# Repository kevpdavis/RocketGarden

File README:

This is a repository for my rocket related projects.

You'll find designs and design tools for rockets, parachutes, printed circuit boards, motors, and whatever else I dabble in.

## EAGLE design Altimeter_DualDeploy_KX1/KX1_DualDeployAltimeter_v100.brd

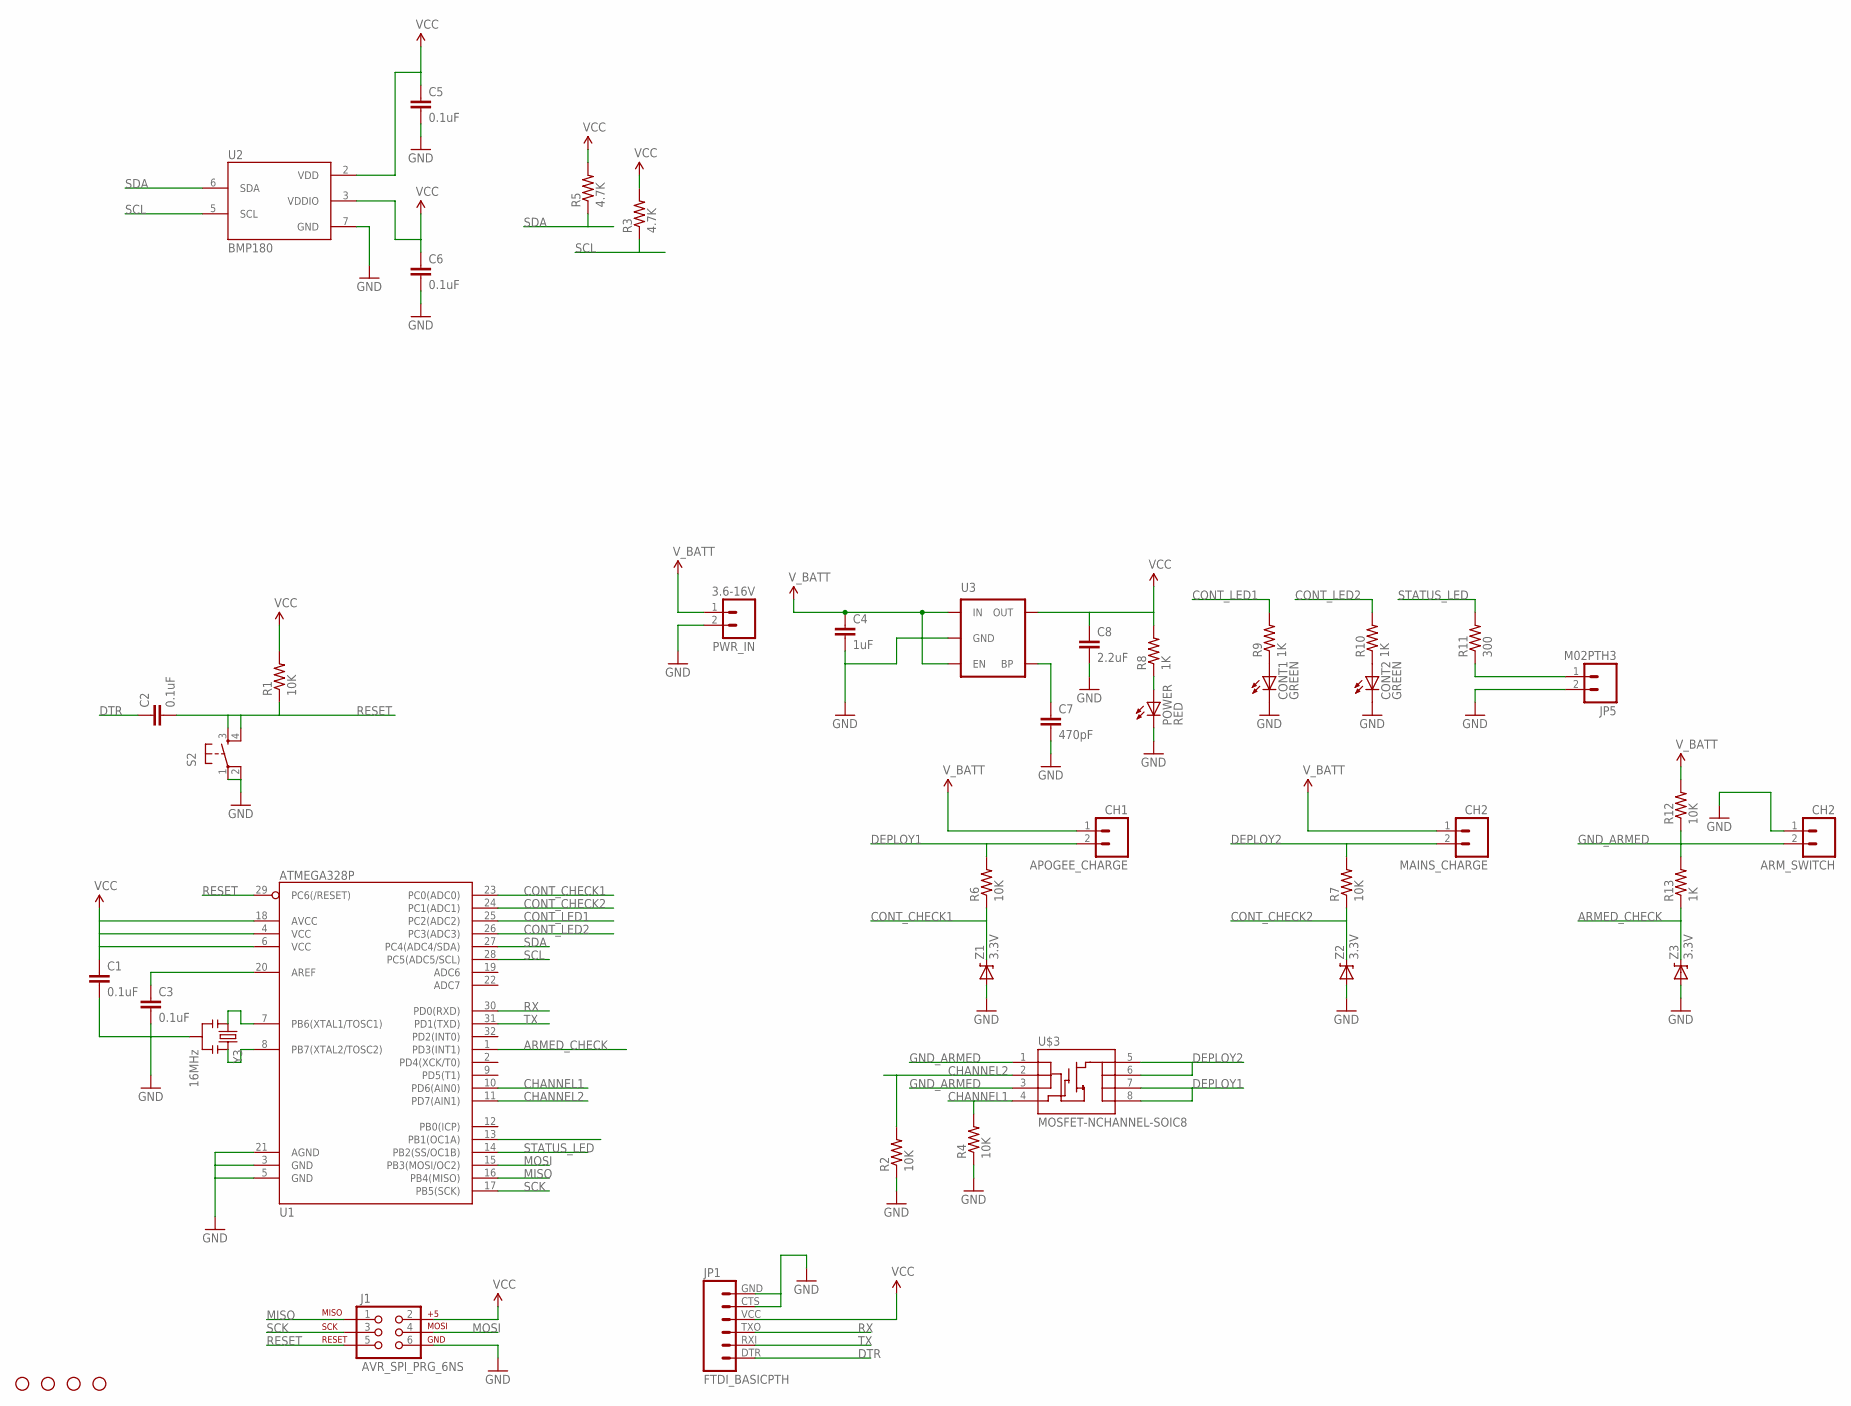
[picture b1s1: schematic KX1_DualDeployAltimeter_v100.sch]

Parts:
APOGEE_CHARGE: CH1; 1X02_LONGPADS
ARM_SWITCH: CH2; 1X02_LONGPADS
C1, C2, C3, C5, C6: 0.1uF; 0603-CAP
C4: 1uF; 0603-CAP
C7: 470pF; 0603-CAP
C8: 2.2uF; 0603-CAP
CONT1, CONT2: GREEN; LED-0603
J1: AVR_SPI_PRG_6NS; 2X3-NS
JP1: FTDI_BASICPTH; FTDI_BASIC
JP5: M02PTH3; 1X02_LONGPADS
MAINS_CHARGE: CH2; 1X02_LONGPADS
POWER: RED; LED-0603
PWR_IN: 3.6-16V; 1X02_LONGPADS
R1, R2, R4, R6, R7, R12: 10K; 0603-RES
R3, R5: 4.7K; 0603-RES
R8, R9, R10, R13: 1K; 0603-RES
R11: 300; 0603-RES
S2: TAC_SWITCHPTH; TACTILE-PTH
STANDOFF1, STANDOFF2, STANDOFF3, STANDOFF4: STAND-OFF
U1: ATMEGA328P; TQFP32-08
U2: BMP180
U3: MIC52053.3V; SOT23-5
U$3: MOSFET-NCHANNEL-SOIC8; SO08
Y3: 16MHz; RESONATOR-SMD
Z1, Z2, Z3: 3.3V; SOD-323

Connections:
ARMED_CHECK: R13.1, U1.1 (PD3(INT1)), Z3.1 (C)
CHANNEL1: R4.2, U1.10 (PD6(AIN0)), U$3.4 (G)
CHANNEL2: R2.2, U1.11 (PD7(AIN1)), U$3.2 (S)
CONT_CHECK1: R6.1, U1.23 (PC0(ADC0)), Z1.1 (C)
CONT_CHECK2: R7.1, U1.24 (PC1(ADC1)), Z2.1 (C)
CONT_LED1: R9.2, U1.25 (PC2(ADC2))
CONT_LED2: R10.2, U1.26 (PC3(ADC3))
DEPLOY1: APOGEE_CHARGE.2, R6.2, U$3.7 (D), U$3.8 (D)
DEPLOY2: MAINS_CHARGE.2, R7.2, U$3.5 (D), U$3.6 (D)
DTR: C2.1, JP1.DTR (1)
GND: ARM_SWITCH.1, C1.2, C3.2, C4.2, C5.2, C6.2, C7.2, C8.2, CONT1.C, CONT2.C, J1.6, JP1.CTS (5), JP1.GND (6), JP5.2, POWER.C, PWR_IN.2, R2.1, R4.1, S2.1, S2.2, U1.3 (GND), U1.5 (GND), U1.21 (AGND), U2.7 (GND), U3.2 (GND), Y3.2, Z1.2 (A), Z2.2 (A), Z3.2 (A)
GND_ARMED: ARM_SWITCH.2, R12.1, R13.2, U$3.1 (S), U$3.3 (S)
MISO: J1.1, U1.16 (PB4(MISO))
MOSI: J1.4, U1.15 (PB3(MOSI/OC2))
unnamed: POWER.A, R8.1
unnamed: CONT1.A, R9.1
unnamed: CONT2.A, R10.1
unnamed: C3.1, U1.20 (AREF)
unnamed: U1.7 (PB6(XTAL1/TOSC1)), Y3.1
unnamed: U1.8 (PB7(XTAL2/TOSC2)), Y3.3
unnamed: JP5.1, R11.1
unnamed: C7.1, U3.4 (BP)
RESET: C2.2, J1.5, R1.1, S2.3, S2.4, U1.29 (PC6(/RESET))
RX: JP1.TXO (3), U1.30 (PD0(RXD))
SCK: J1.3, U1.17 (PB5(SCK))
SCL: R3.1, U1.28 (PC5(ADC5/SCL)), U2.5 (SCL)
SDA: R5.1, U1.27 (PC4(ADC4/SDA)), U2.6 (SDA)
STATUS_LED: R11.2, U1.14 (PB2(SS/OC1B))
TX: JP1.RXI (2), U1.31 (PD1(TXD))
VCC: C1.1, C5.1, C6.1, C8.1, J1.2, JP1.VCC (4), R1.2, R3.2, R5.2, R8.2, U1.4 (VCC), U1.6 (VCC), U1.18 (AVCC), U2.2 (VDD), U2.3 (VDDIO), U3.5 (OUT)
V_BATT: APOGEE_CHARGE.1, C4.1, MAINS_CHARGE.1, PWR_IN.1, R12.2, U3.1 (IN), U3.3 (EN)

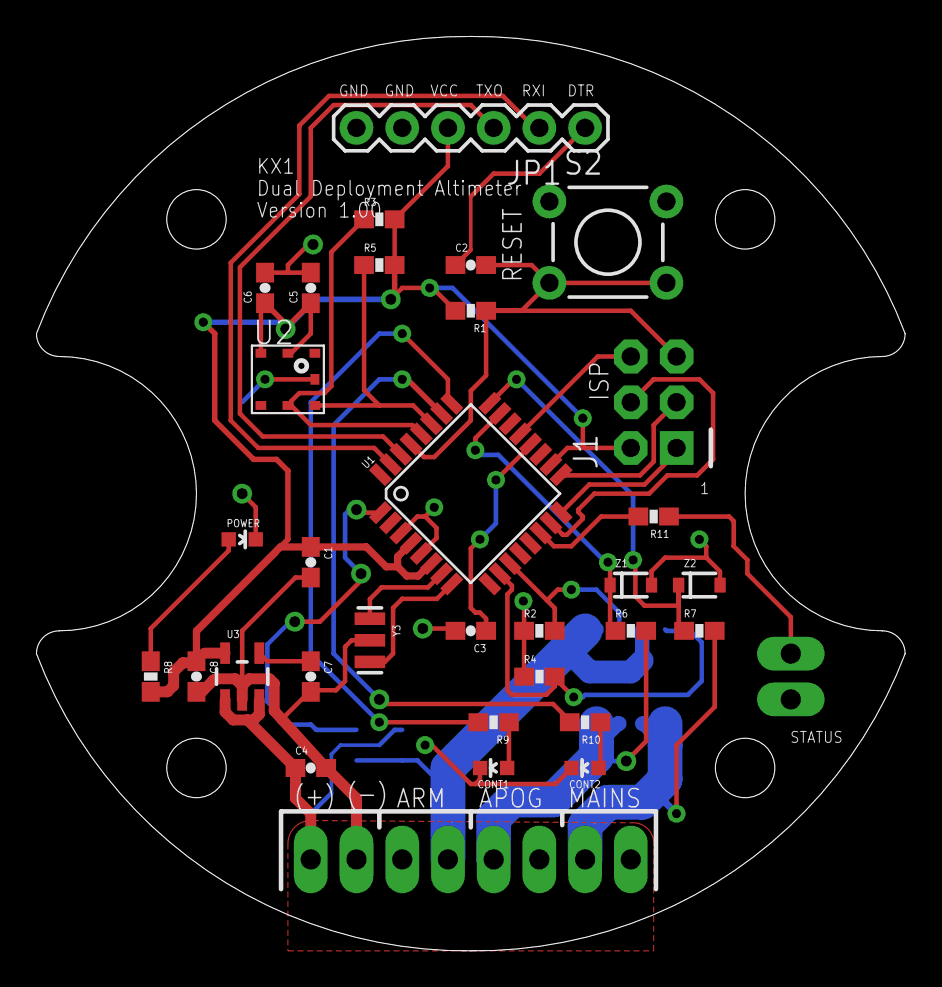
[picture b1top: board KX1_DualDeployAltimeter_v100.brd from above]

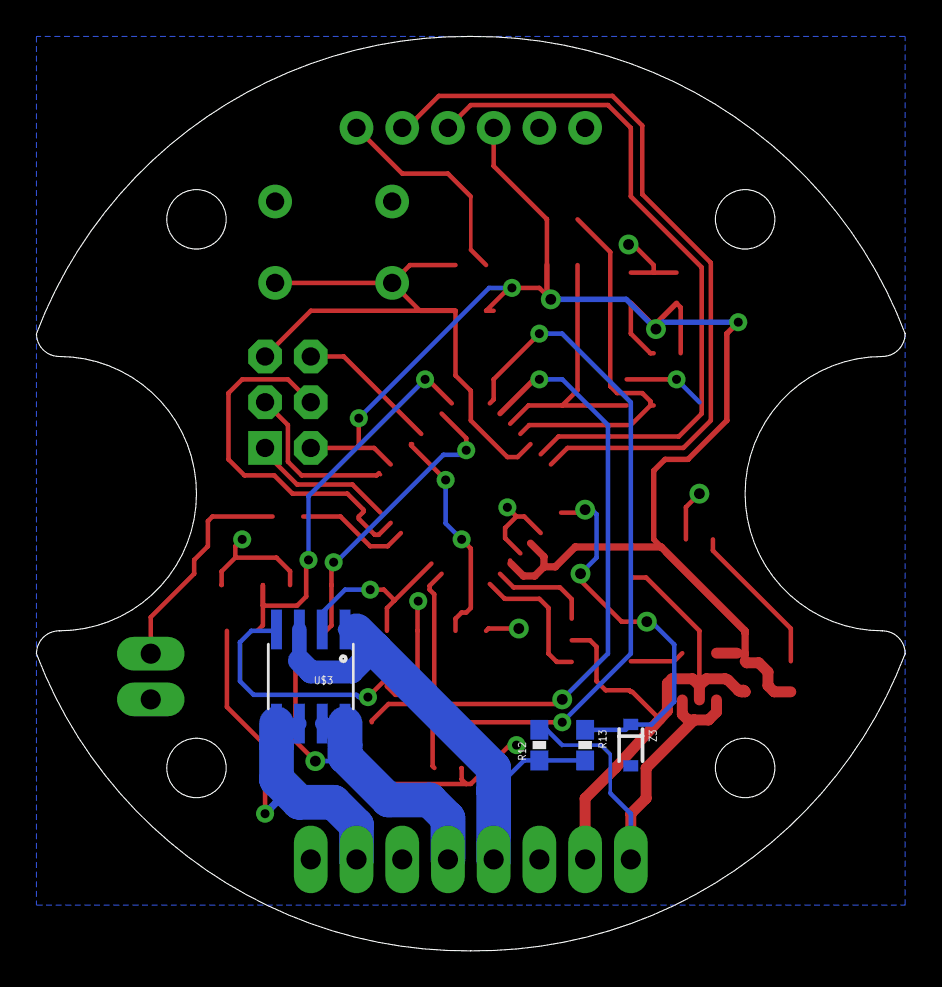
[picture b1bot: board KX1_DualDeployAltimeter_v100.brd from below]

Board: 2 copper layers, 48.3 x 50.8 mm, 44 parts (4 on the bottom side), 31 nets.

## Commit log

2013-11-27 added Altimeter project
2013-11-28 Added altimeter design files
2013-11-29 Updated board design. Added .gitignore to ignore CAM output files
2013-11-29 Updated design. Added via tenting, fixed silkscreen issues.
2013-11-29 Removed .zip files. Added *.zip to .gitignore.
2013-11-29 Updated .gitignore
2013-11-29 Fixed unconnected trace and widened deployment charge traces.
2013-11-30 Updated .gitignore to ignore temporary files preceeded by ~.
2013-11-30 Updated board layout. Tweaked silkscreen. Added V_BATT plane.
2013-11-30 Updated parts list
2014-12-20 '''Altimeter Software''' Added altimeter software sketch with some skeleton code.
2014-12-20 Updated skeleton program flow and logic

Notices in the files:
parts and their libraries:
SparkFun-DigitalIC: Licensing: CC v3.0 Share-Alike You are welcome to use this library for commercial purposes.
